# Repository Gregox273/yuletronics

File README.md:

# Yuletronics 2016

/pcb contains main board  
/pcb_2 contains second board that slots into first  
  
Greg Brooks 2016  
Original design D Turner and A Greig

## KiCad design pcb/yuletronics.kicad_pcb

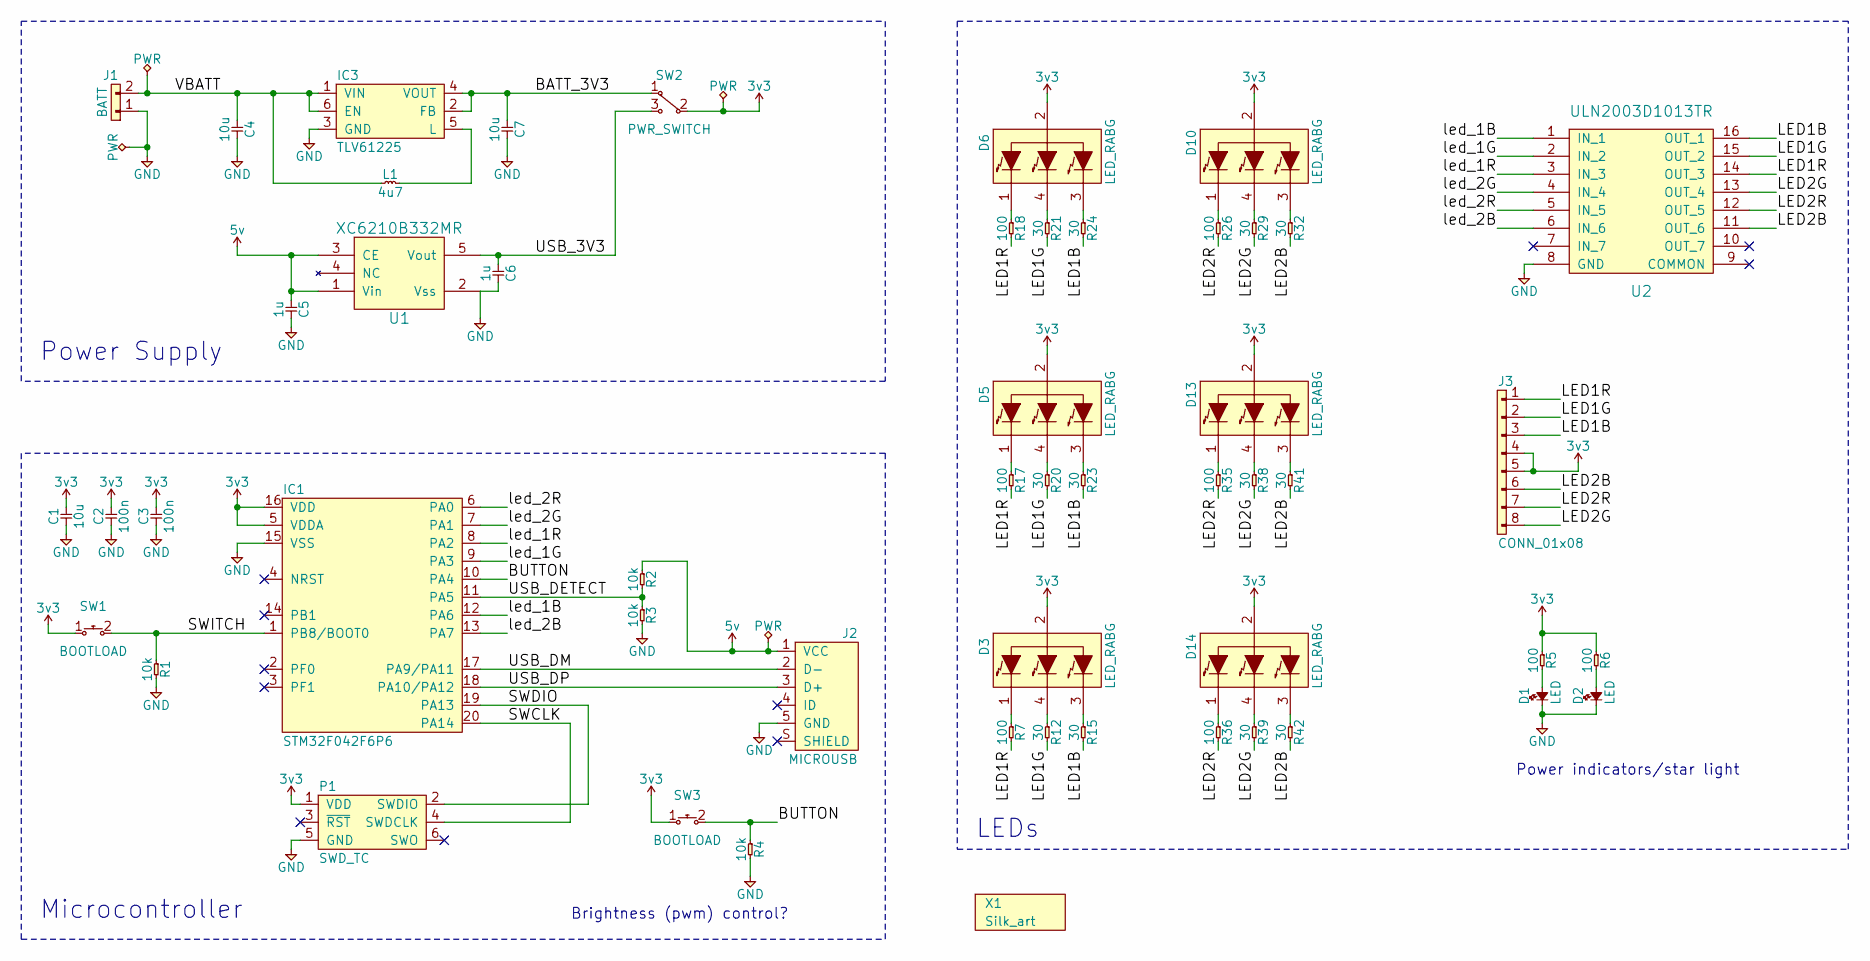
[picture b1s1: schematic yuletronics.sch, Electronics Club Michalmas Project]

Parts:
C1, C4, C7: 10u; 0805; Farnell 2320851
C2, C3: 100n; 0805; Farnell 1759265
C5, C6: 1u; 0805; Farnell 2320853
D1, D2: LED; 0805-LED; Farnell 2099242
D3, D5, D6, D10, D13, D14: LED_RABG; CREE_RGB_LED; Farnell 1855553
IC1: STM32F042F6P6; TSSOP-20; Farnell 2469549
IC3: TLV61225; SC-70-6; Farnell 2492362
J1: BATT; AAA_HOLDER; Farnell 1702632
J2: MICROUSB; MICROUSB_MOLEX_47589-0001; Farnell 1568023
J3: CONN_01x08; Interboard; Farnell Value
L1: 4u7; 2016M; Farnell 2616849
P1: SWD_TC; TC2030-NL
R1, R2, R3, R4: 10k; 0805; Farnell 9332391
R5, R6, R7, R17, R18, R26, R35, R36: 100; 0805; Farnell 9332375
R12, R15, R20, R21, R23, R24, R29, R32, R38, R39, R41, R42: 30; 0805; Farnell 9333029
SW1, SW3: BOOTLOAD; MOM_SWITCH; Farnell 2056809
SW2: PWR_SWITCH; SPDT_SWITCH; Farnell 1201430
U1: XC6210B332MR; SOT-23-5; Farnell 1057803
U2: ULN2003D1013TR; SOIC-16; Farnell 1467825
X1: Silk_art; tree_silk_scaled; Farnell Value

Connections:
3v3: C1.2, C2.2, C3.2, D3.2 (COMMON_ANODE), D5.2 (COMMON_ANODE), D6.2 (COMMON_ANODE), D10.2 (COMMON_ANODE), D13.2 (COMMON_ANODE), D14.2 (COMMON_ANODE), IC1.5 (VDDA), IC1.16 (VDD), J3.4, J3.5, P1.1 (VDD), R5.1, R6.1, SW1.1, SW2.2, SW3.1
5v: C5.1, J2.1 (VCC), R2.1, U1.1 (Vin), U1.3 (CE)
/BATT_3V3: C7.1, IC3.2 (FB), IC3.4 (VOUT), SW2.1
/BUTTON: IC1.10 (PA4), R4.1, SW3.2
/LED1B: J3.3, R15.2, R23.2, R24.2, U2.16 (OUT_1)
/LED1G: J3.2, R12.2, R20.2, R21.2, U2.15 (OUT_2)
/LED1R: J3.1, R7.2, R17.2, R18.2, U2.14 (OUT_3)
/LED2B: J3.6, R32.2, R41.2, R42.2, U2.11 (OUT_6)
/LED2G: J3.8, R29.2, R38.2, R39.2, U2.13 (OUT_4)
/LED2R: J3.7, R26.2, R35.2, R36.2, U2.12 (OUT_5)
/SWCLK: IC1.20 (PA14), P1.4 (SWDCLK)
/SWDIO: IC1.19 (PA13), P1.2 (SWDIO)
/SWITCH: IC1.1 (PB8/BOOT0), R1.1, SW1.2
/USB_3V3: C6.1, SW2.3, U1.5 (Vout)
/USB_DETECT: IC1.11 (PA5), R2.2, R3.1
/USB_DM: IC1.17 (PA9/PA11), J2.2 (D-)
/USB_DP: IC1.18 (PA10/PA12), J2.3 (D+)
/VBATT: C4.1, IC3.1 (VIN), IC3.6 (EN), J1.2, L1.1
/led_1B: IC1.12 (PA6), U2.1 (IN_1)
/led_1G: IC1.9 (PA3), U2.2 (IN_2)
/led_1R: IC1.8 (PA2), U2.3 (IN_3)
/led_2B: IC1.13 (PA7), U2.6 (IN_6)
/led_2G: IC1.7 (PA1), U2.4 (IN_4)
/led_2R: IC1.6 (PA0), U2.5 (IN_5)
GND: C1.1, C2.1, C3.1, C4.2, C5.2, C6.2, C7.2, D1.1, D2.1, IC1.15 (VSS), IC3.3 (GND), J1.1, J2.5 (GND), P1.5 (GND), R1.2, R3.2, R4.2, U1.2 (Vss), U2.8 (GND)
unnamed: D1.2, R5.2
unnamed: D2.2, R6.2
unnamed: D3.1 (RED_CATHODE), R7.1
unnamed: D3.3 (BLUE_CATHODE), R15.1
unnamed: D3.4 (GREEN_CATHODE), R12.1
unnamed: D5.1 (RED_CATHODE), R17.1
unnamed: D5.3 (BLUE_CATHODE), R23.1
unnamed: D5.4 (GREEN_CATHODE), R20.1
unnamed: D6.1 (RED_CATHODE), R18.1
unnamed: D6.3 (BLUE_CATHODE), R24.1
unnamed: D6.4 (GREEN_CATHODE), R21.1
unnamed: D10.1 (RED_CATHODE), R26.1
unnamed: D10.3 (BLUE_CATHODE), R32.1
unnamed: D10.4 (GREEN_CATHODE), R29.1
unnamed: D13.1 (RED_CATHODE), R35.1
unnamed: D13.3 (BLUE_CATHODE), R41.1
unnamed: D13.4 (GREEN_CATHODE), R38.1
unnamed: D14.1 (RED_CATHODE), R36.1
unnamed: D14.3 (BLUE_CATHODE), R42.1
unnamed: D14.4 (GREEN_CATHODE), R39.1
unnamed: IC3.5 (L), L1.2

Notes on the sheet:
Power Supply
Microcontroller
LEDs
Brightness (pwm) control?
Power indicators/star light

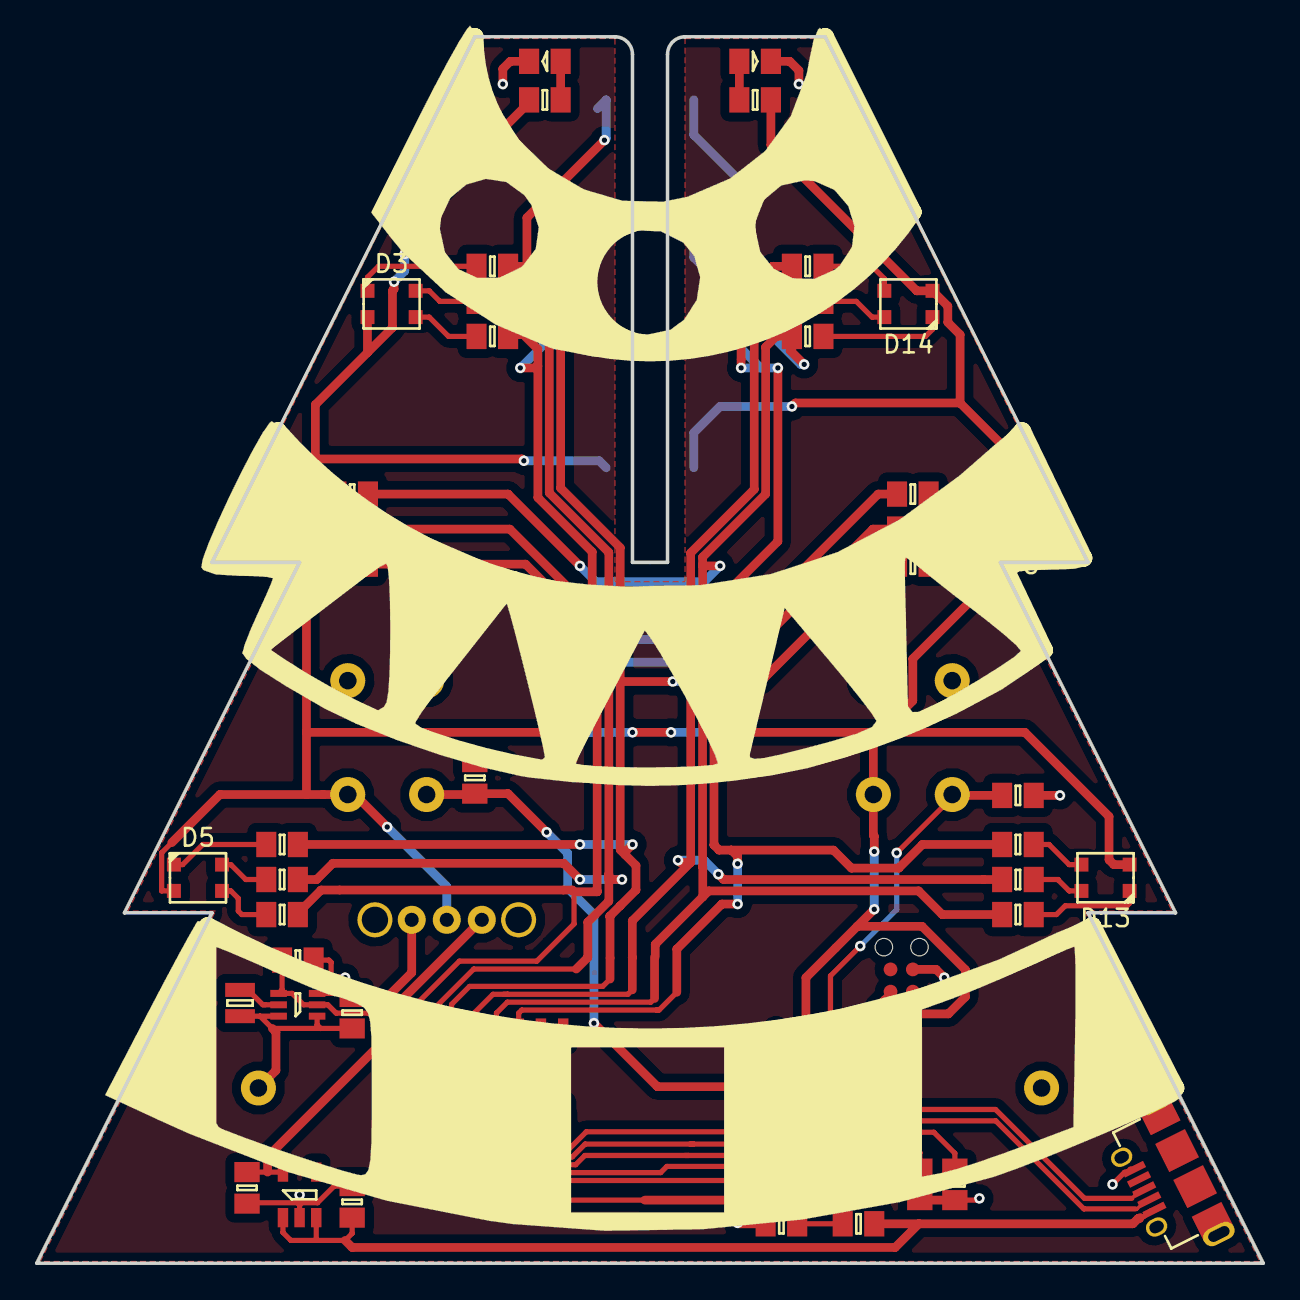
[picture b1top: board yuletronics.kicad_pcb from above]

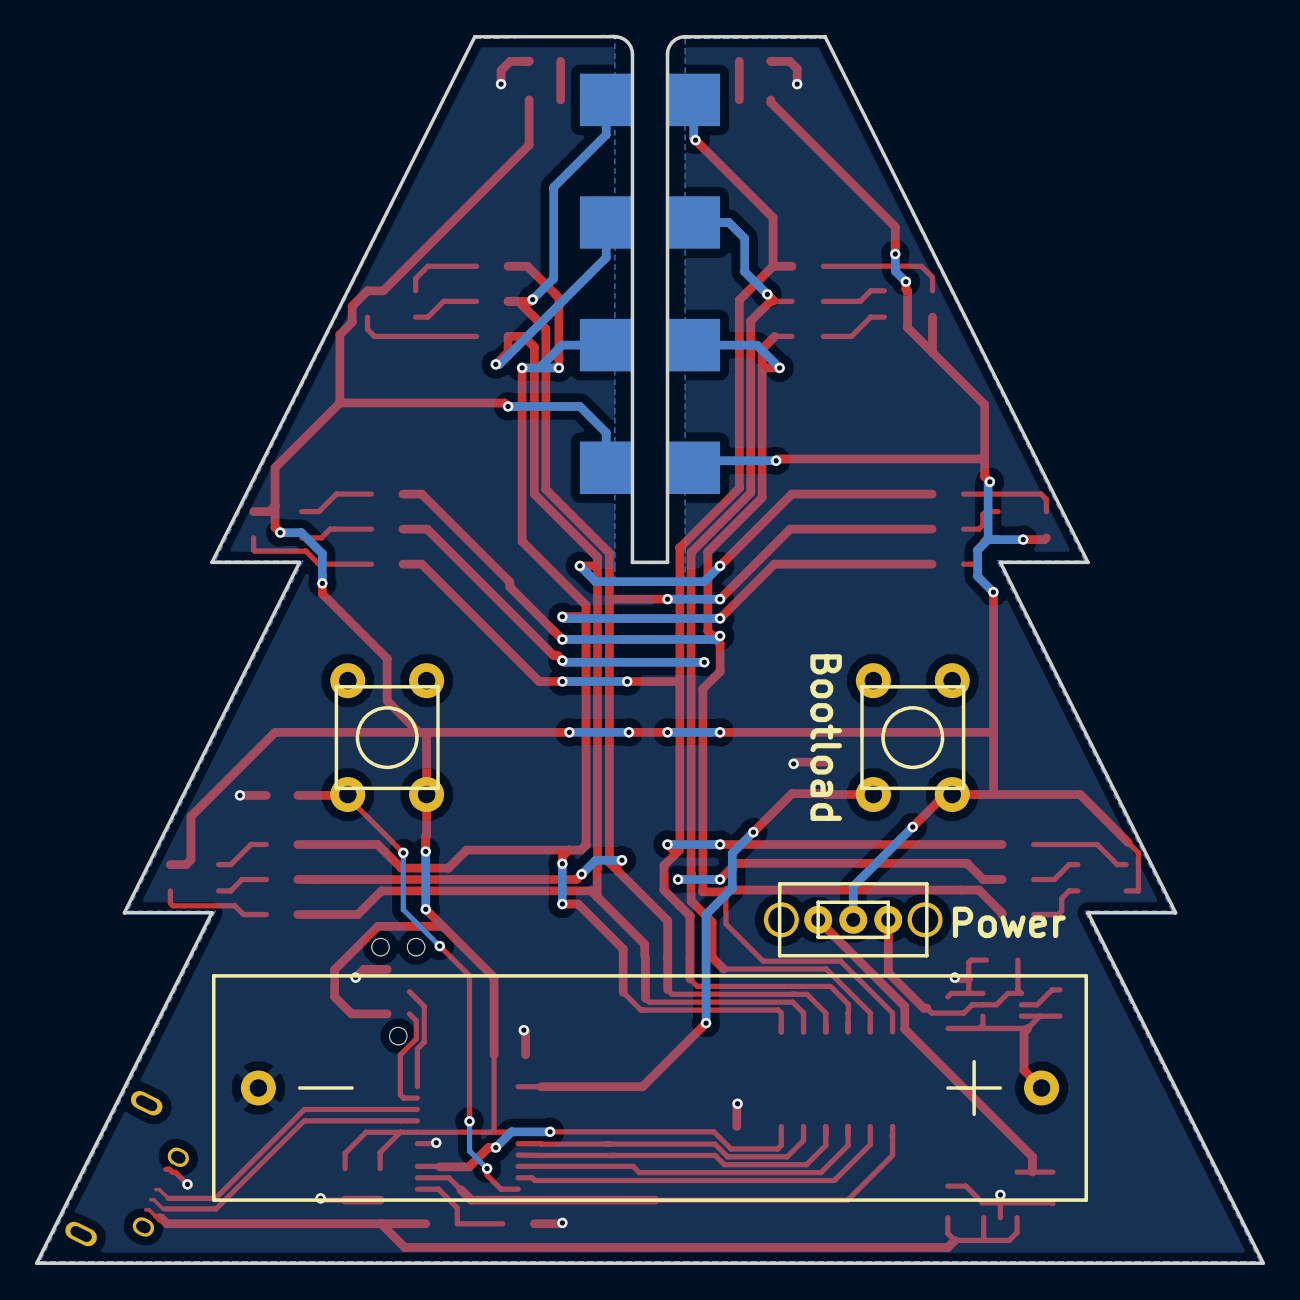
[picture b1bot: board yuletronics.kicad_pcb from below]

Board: 2 copper layers, 70.0 x 70.0 mm, 52 parts (5 on the bottom side), 46 nets.

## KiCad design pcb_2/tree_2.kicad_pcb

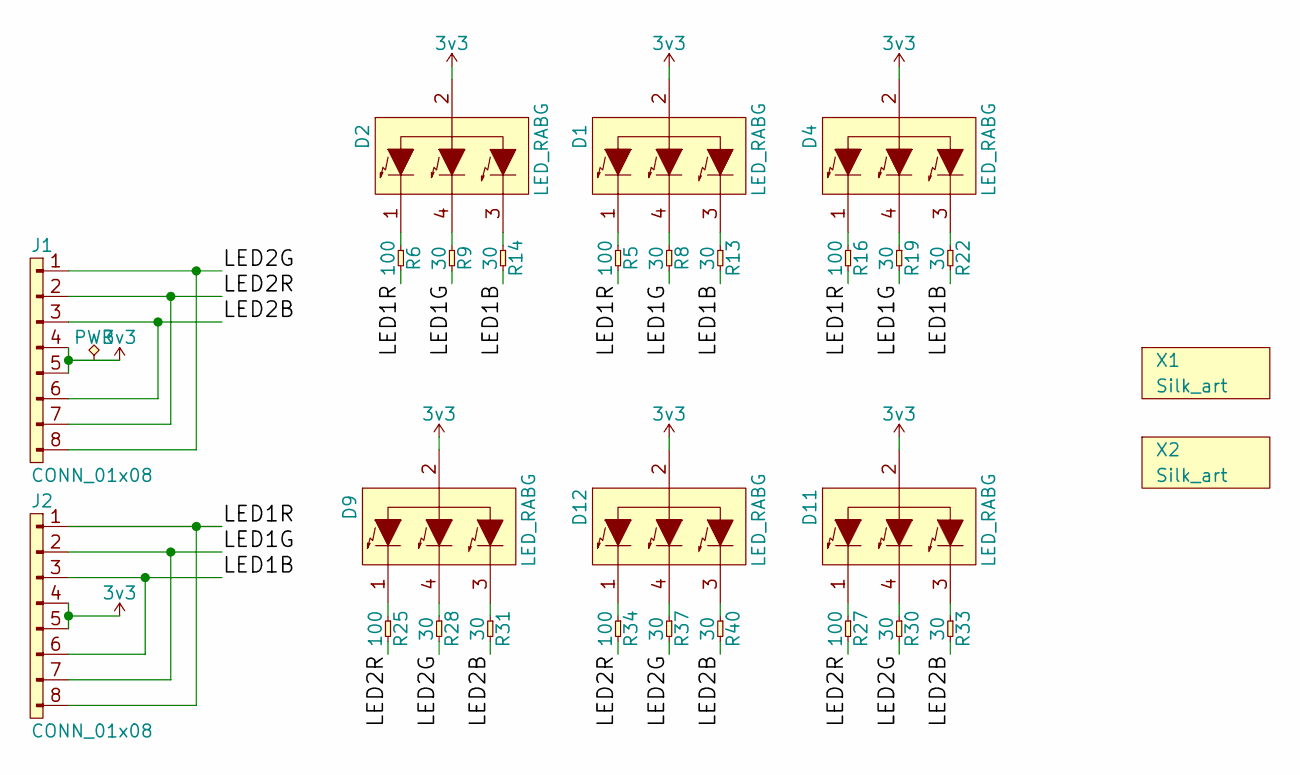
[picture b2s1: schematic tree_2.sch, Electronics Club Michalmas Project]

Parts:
D1, D2, D4, D9, D11, D12: LED_RABG; CREE_RGB_LED; Digikey Value
J1, J2: CONN_01x08; Interboard; Digikey Value
R5, R6, R16, R25, R27, R34: 100; 0805; Digikey Value
R8, R9, R13, R14, R19, R22, R28, R30, R31, R33, R37, R40: 30; 0805; Digikey Value
X1, X2: Silk_art; tree_silk_scaled; Digikey Value

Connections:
3v3: D1.2 (COMMON_ANODE), D2.2 (COMMON_ANODE), D4.2 (COMMON_ANODE), D9.2 (COMMON_ANODE), D11.2 (COMMON_ANODE), D12.2 (COMMON_ANODE), J1.4, J1.5, J2.4, J2.5
/LED1B: J2.3, J2.6, R13.2, R14.2, R22.2
/LED1G: J2.2, J2.7, R8.2, R9.2, R19.2
/LED1R: J2.1, J2.8, R5.2, R6.2, R16.2
/LED2B: J1.3, J1.6, R31.2, R33.2, R40.2
/LED2G: J1.1, J1.8, R28.2, R30.2, R37.2
/LED2R: J1.2, J1.7, R25.2, R27.2, R34.2
unnamed: D1.1 (RED_CATHODE), R5.1
unnamed: D1.3 (BLUE_CATHODE), R13.1
unnamed: D1.4 (GREEN_CATHODE), R8.1
unnamed: D2.1 (RED_CATHODE), R6.1
unnamed: D2.3 (BLUE_CATHODE), R14.1
unnamed: D2.4 (GREEN_CATHODE), R9.1
unnamed: D4.1 (RED_CATHODE), R16.1
unnamed: D4.3 (BLUE_CATHODE), R22.1
unnamed: D4.4 (GREEN_CATHODE), R19.1
unnamed: D9.1 (RED_CATHODE), R25.1
unnamed: D9.3 (BLUE_CATHODE), R31.1
unnamed: D9.4 (GREEN_CATHODE), R28.1
unnamed: D11.1 (RED_CATHODE), R27.1
unnamed: D11.3 (BLUE_CATHODE), R33.1
unnamed: D11.4 (GREEN_CATHODE), R30.1
unnamed: D12.1 (RED_CATHODE), R34.1
unnamed: D12.3 (BLUE_CATHODE), R40.1
unnamed: D12.4 (GREEN_CATHODE), R37.1

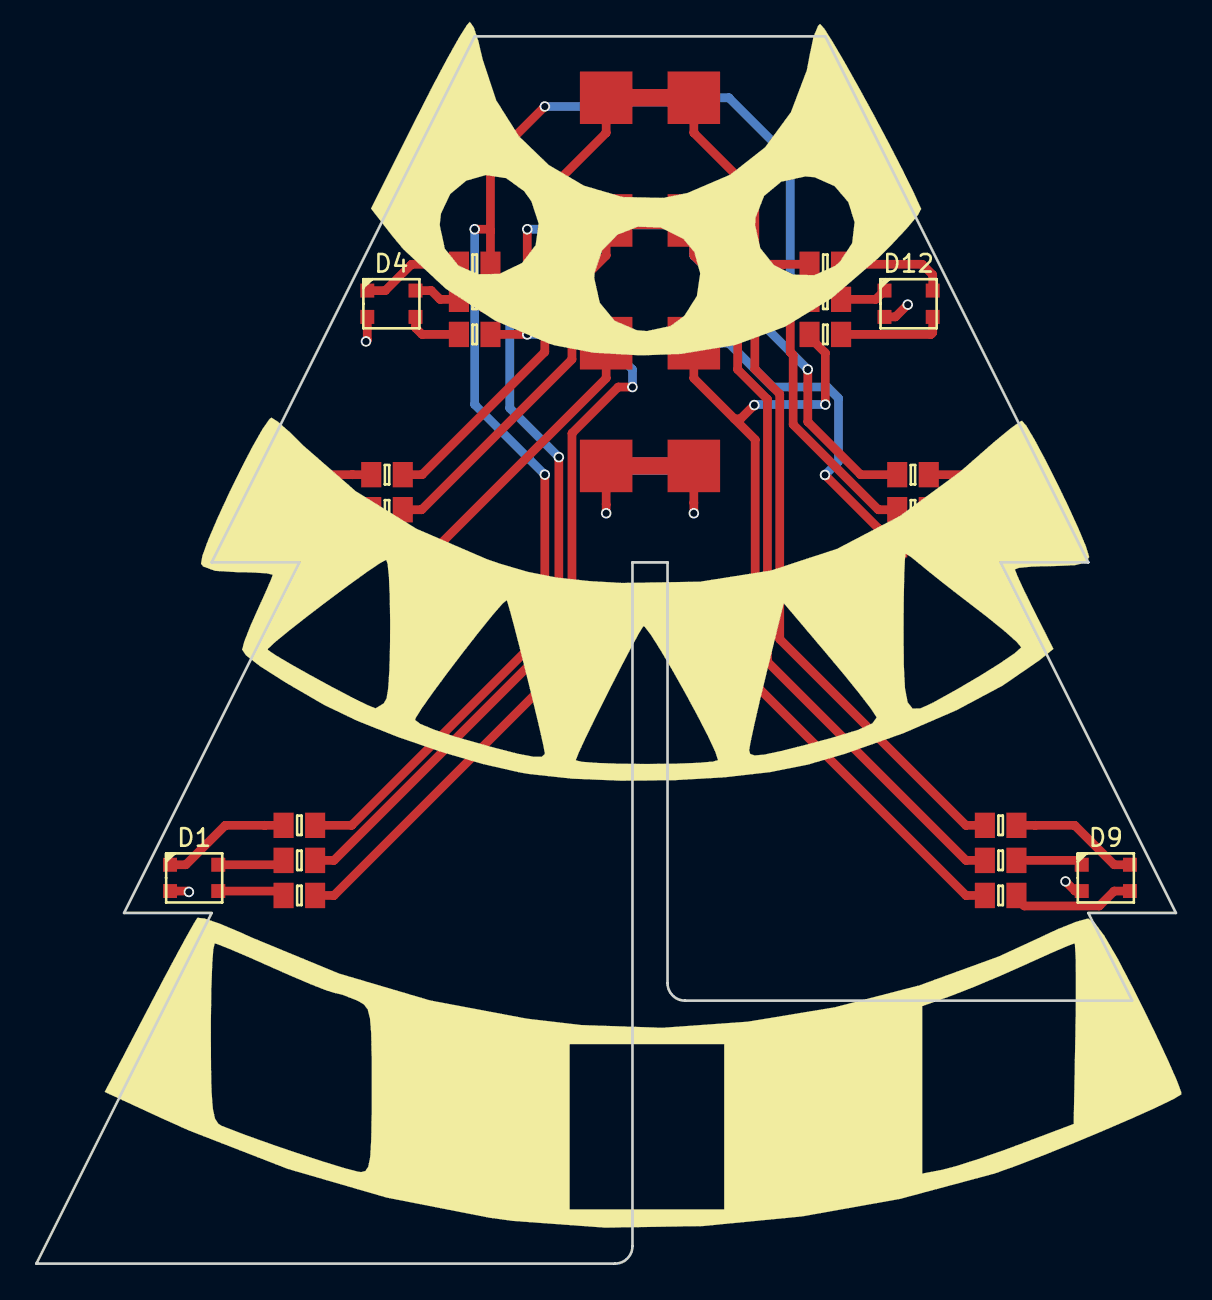
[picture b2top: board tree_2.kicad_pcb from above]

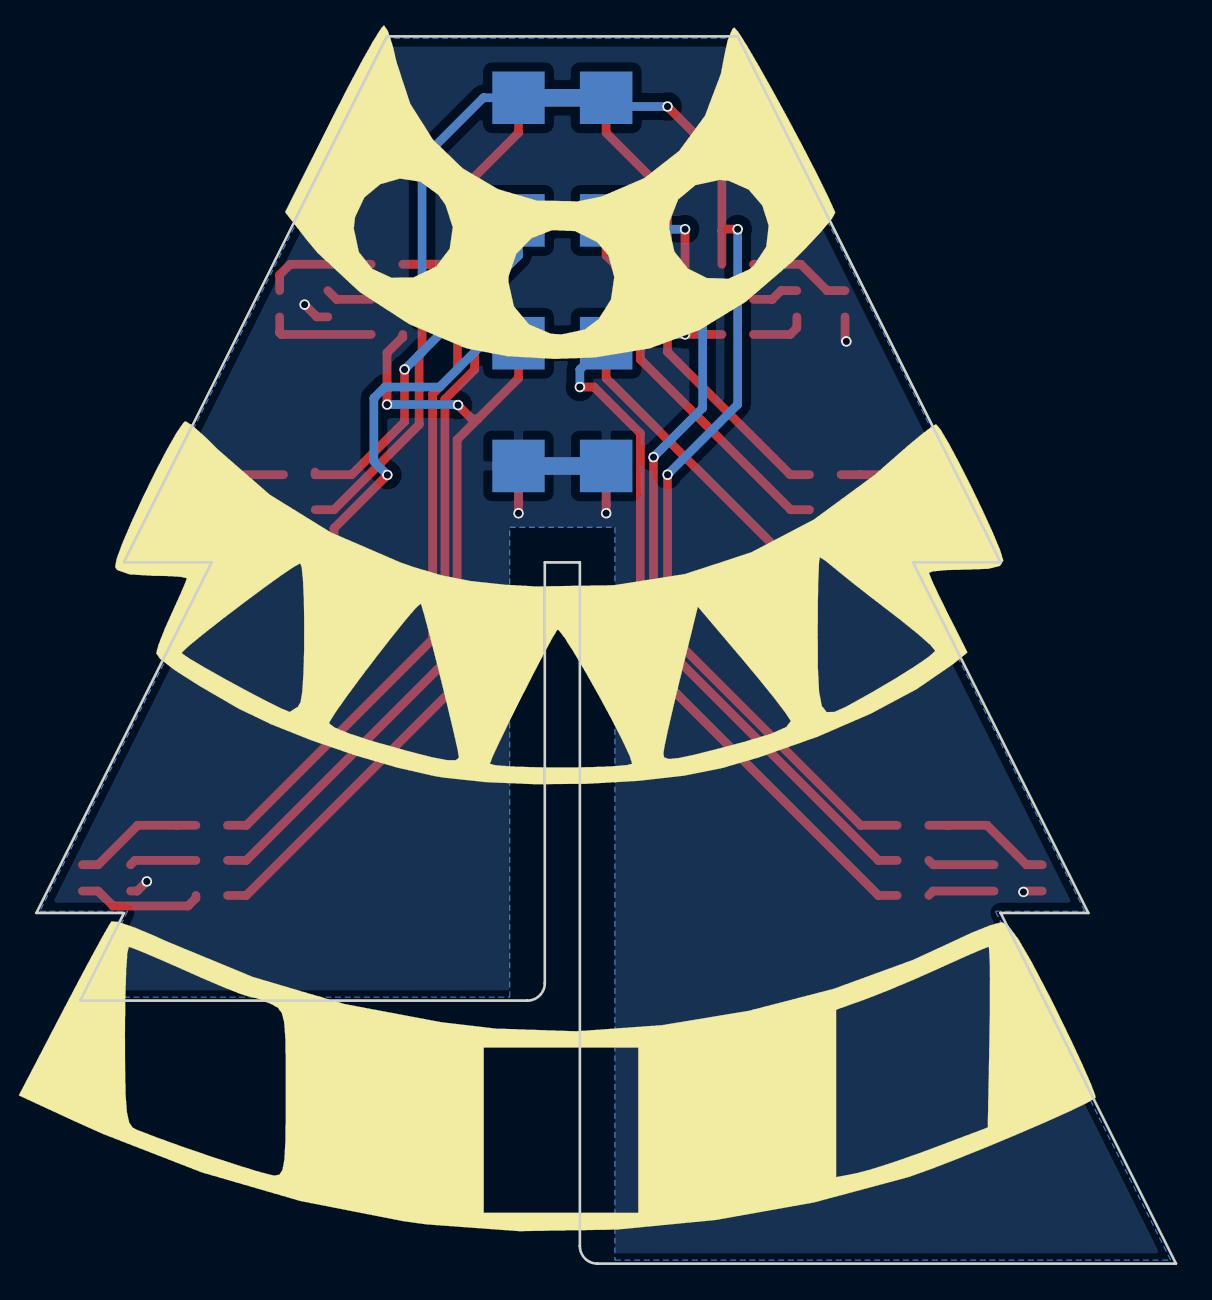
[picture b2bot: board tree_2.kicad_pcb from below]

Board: 2 copper layers, 65.0 x 70.0 mm, 28 parts (2 on the bottom side), 25 nets.

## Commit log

2016-10-15 Version 1
2016-10-15 Remove old gerbers and create them for secondary board
2016-10-15 Move pcb2 gerbers and remove original bom and xml files
2016-10-19 Fix circuit to account for LED currents: change resistor values, upgrade LDO regulator, use transistor array
2016-10-21 Set up Makefile and firmware template
2016-10-21 Further configuration of ChibiOS
2016-10-22 Further configuration, create initial board.h file
2016-11-02 Update config to enable pwm
2016-11-02 Begin setting up pwm timer in firmware
2016-11-03 Update LED farnell code, generate BOM
2016-11-03 Tidy BOM
2016-11-07 Work on firmware structure
2016-11-08 Work on LED server/client threads
2016-11-09 First iteration of led threads complete
2016-11-13 Add commands to Makefile
2016-11-13 Firmware changes, need to protect globals with mutex, replacing mailbox
2016-11-13 Small changes
2016-11-13 Add mutexes, restructure interaction between threads and interrupt
2016-11-18 Fix syntax errors
2016-11-19 Edit makefile, create dxfs for soldering stencil
2016-11-21 Update firmware after first test on hardware
2016-11-21 Further improvements and attempt to get brightness control working
2016-11-21 Implement brightness control (and small fixes)
2019-12-11 Add stickerbom pdfs
2019-12-12 Add binary
